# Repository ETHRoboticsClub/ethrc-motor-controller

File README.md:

<h1 align="center">ETHRC Motor Controller</h1>

<p align="center" width="100%">
  
</p>

***

<p align="center">
  
&nbsp; &nbsp; &nbsp; &nbsp;
  
</p>

***

## SPECIFICATIONS

| Parameter | ETHRC Motor Controller v1.0| 
| --- | --- |
| Voltage Input | 33 - 58.8V |
| Peak Electrical Power | TBD |
| Mass | TBD |
| Peak Phase Current | TBD |
| Communication | EtherCat, 5Mbps CAN-FD and SWD interface |
| Cooling | TBD|
| Positioning | 1x Onboard 14-bit Encoder and one external encoder |
| Control rate | TBD |
| PWM Switching Rate | TBD |
| MCU | STM32G474 |
| Dimensions | 88.0 × 88.0 mm |

***

## DIRECTORY STRUCTURE

    .
    ├─ Computations       # Misc calculations
    ├─ DXF_SVG            # Vector graphics
    ├─ HTML               # HTML files for generated webpage
    ├─ Images             # Pictures and renders
    │
    ├─ kibot_resources    # External resources for KiBot
    │  ├─ colors          # Color theme for KiCad
    │  ├─ fonts           # Fonts used in the project
    │  ├─ scripts         # External scripts used with KiBot
    │  └─ templates       # Templates for KiBot generated reports
    │
    ├─ kibot_yaml         # KiBot YAML config files
    ├─ KiRI               # KiRI (PCB diff viewer) files
    │
    ├─ lib                # KiCad footprint and symbol libraries
    │  ├─ 3d_models       # Component 3D models
    │  ├─ lib_fp          # Footprint libraries
    │  └─ lib_sym         # Symbol libraries
    │
    ├─ Logos              # Logos
    │
    ├─ Manufacturing      # Assembly and fabrication documents
    │  ├─ Assembly        # Assembly documents (BoM, pos, notes)
    │  │
    │  └─ Fabrication     # Fabrication documents (ZIP, notes)
    │     ├─ Drill Tables # CSV drill tables
    │     └─ Gerbers      # Gerbers
    │
    ├─ Report             # Reports for ERC/DRC
    ├─ Schematic          # PDF of schematic
    ├─ Templates          # Title block templates
    ├─ Testing
    │  └─ Testpoints      # Testpoints tables      
    │
    └─ Variants           # Outputs for assembly variants

***

## FIRMWARE

***

## CREDITS

Schematic is largely inspired by the moteus controllers designed by Josh Pieper and amulet motion controller designed by Vincent Nguyen. They were modified to meet our own specifications. The CI/CD workflow and the templates for this KiCad 9.0 project was forked from https://github.com/nguyen-v/KDT_Hierarchical_KiBot created by Vincent Nguyen.
***

## PHOTOS

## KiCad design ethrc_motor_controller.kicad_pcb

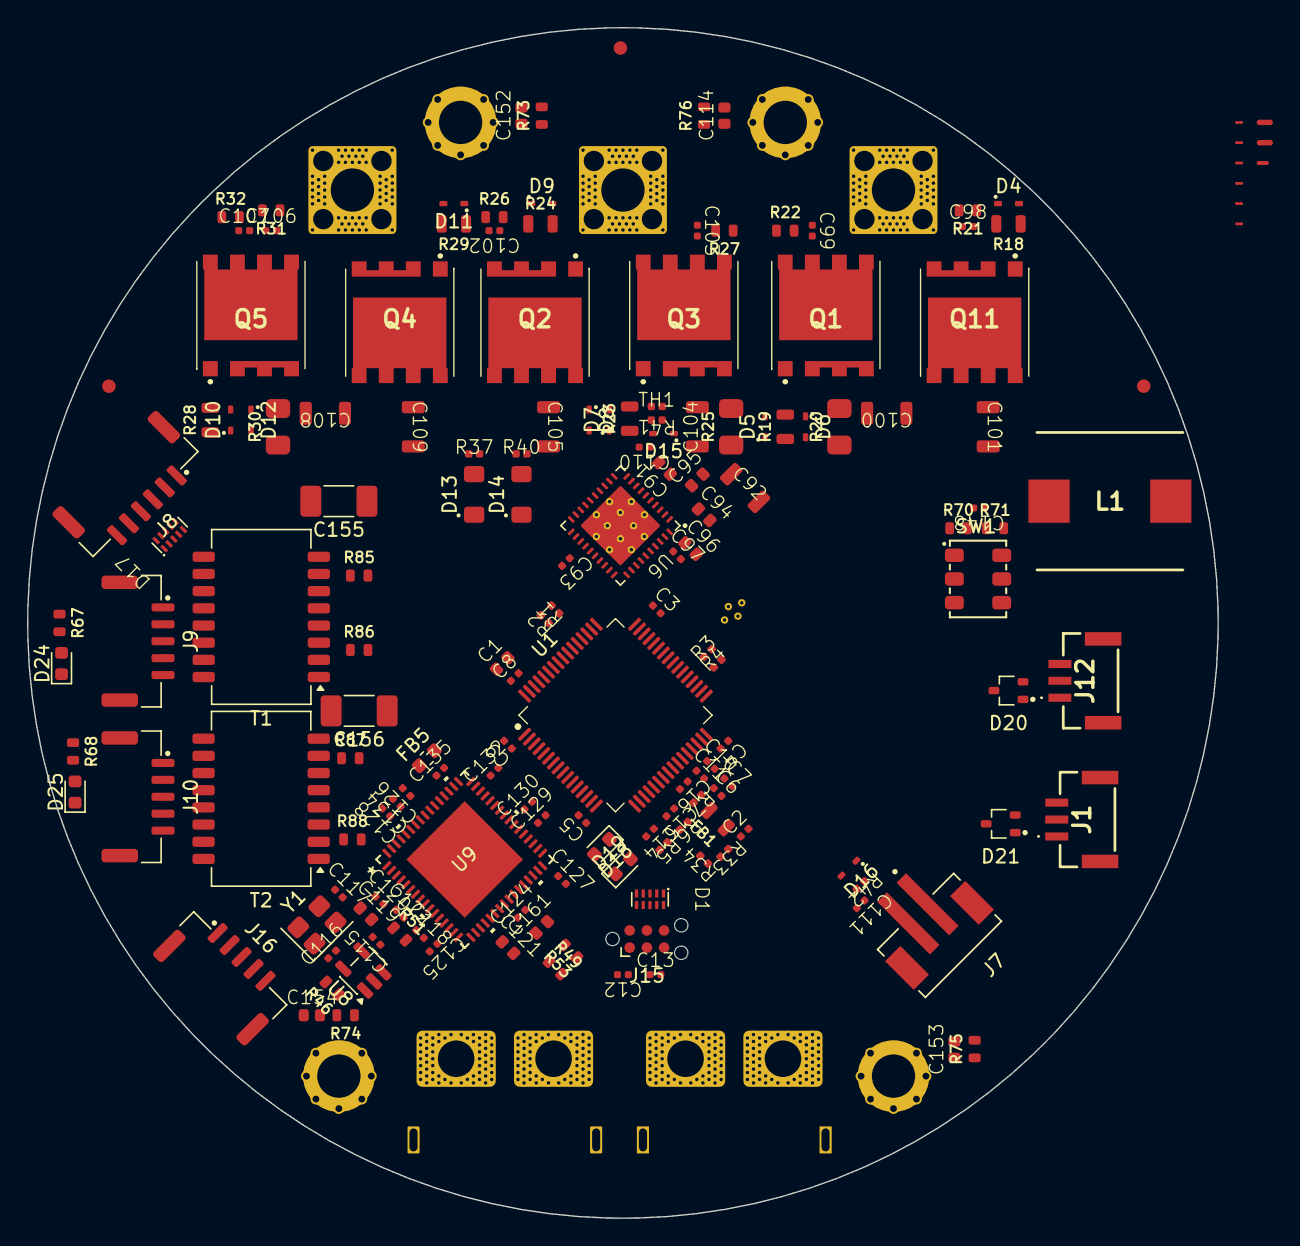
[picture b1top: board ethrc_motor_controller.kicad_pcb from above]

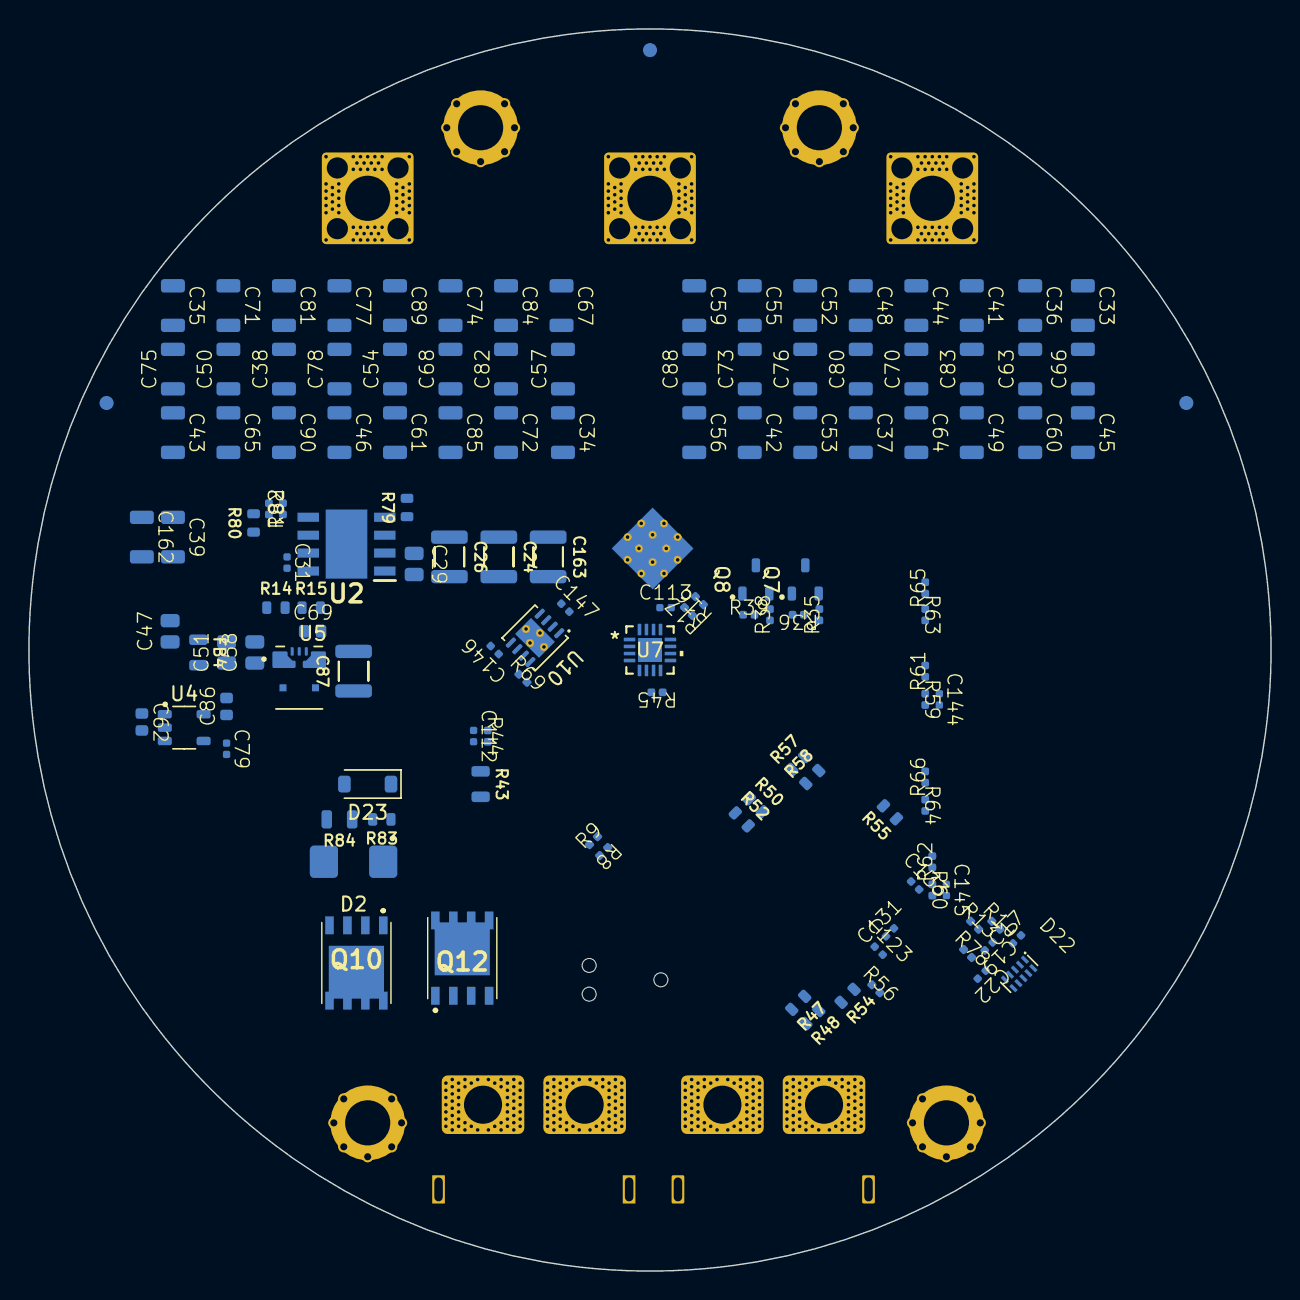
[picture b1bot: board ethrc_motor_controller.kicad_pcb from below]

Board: 6 copper layers, 88.0 x 88.0 mm, 306 parts (131 on the bottom side), 158 nets, no tracks yet.

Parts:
C1, C86: 4u7 X7R 16V; C_0603_1608_DensityHigh
C2, C6, C9: 1u X7R 10V; C_0402_1005_DensityHigh
C3, C4, C5, C8, C10, C11, C12, C13, C110, C111, C112, C146, C147: 100n X7R 50V; C_0402_1005_DensityHigh
C7: 4u7 X5R 25V; C_0402_1005_DensityHigh
C14, C15, C16: 1n X7R 25V; C_0402_1005_DensityHigh
C17, C19, C22: 1n; C_0402_1005_DensityHigh
C24, C26, C163: 1u; C_1210_3225_DensityHigh
C29, C58: 100n; C_0805_2012_DensityHigh
C31, C115, C118, C120, C122, C123, C124, C125, C126, C127, C128, C129, C130, C131, C132, C133, C134, C135: 100n; C_0402_1005_DensityHigh
C33, C34, C35, C36, C37, C38, C41, C42, C43, C44, C45, C46, C48, C49, C50, C52, C53, C54, C55, C56, C57, C59, C60, C61, C63, C64, C65, C66, C67, C68, C70, C71, C72, C73, C74, C75, C76, C77, C78, C80, C81, C82, C83, C84, C85, C88, C89, C90: 4u7 X7R 100V; C_1206_3216_DensityHigh
C39, C162: 47u; C_1206_3216_DensityHigh
C47: 2u2 X7R 100V; C_0805_2012_DensityHigh
C51: 10u; C_0805_2012_DensityHigh
C62, C91, C96: 1u X7R 25V; C_0603_1608_DensityHigh
C69: 10n; C_0603_1608_DensityHigh
C79: 10n X7R 100V; C_0402_1005_DensityHigh
C87: 22u; C_1210_3225_DensityHigh
C92, C101, C105, C109: 4u7 X7R 100V; C_1206_3216_DensityHighest
C93: 100n X7R 16V; C_0402_1005_DensityHigh
C94: 47n X7R 100V; C_0603_1608_DensityHigh
C95: 100n X7R 100V; C_0603_1608_DensityHigh
C97: 1u X7R 6.3V; C_0402_1005_DensityHigh
C98, C99, C102, C103, C106, C107: 3n3 X7R 100V; C_0402_1005_DensityHigh
C100, C104, C108: 100n X7R 100V; C_1206_3216_DensityHighest
C113: 1u; C_0402_1005_DensityHigh
C114, C152, C153, C154: 1n X7R 1kV; C_0603_1608_DensityHigh
C116, C117: 10p C0G; C_0402_1005_DensityHigh
C119, C121, C161: 1u; C_0603_1608_DensityHigh
C144, C145: 0.022u; C_0402_1005_DensityHigh
C148: 4n7 X7R 100V; C_0402_1005_DensityHigh
C155, C156: 1n X7R 2kV; C_1808_4520Metric
D1: PESD4USB3U-TBSX; SOT1176D
D2: SMBJ60A; D_SMB
D4, D5, D6, D7, D8, D9, D10, D11, D12, D15, D16: BAT41KFILM; D_SOD-523
D13: YELLOW; LED_SM1206
D14: GREEN; LED_SM1206
D17: PESD4USB5B-TBSX; SOT1176D
D18: Red; LED_0603_1608Metric
D19, D24, D25: Green; LED_0603_1608Metric
D20, D21: PESD2CANFD24V-UX; SOT95P230X117-3N
D22: PESD4USB5B; SOT1176D
D23: BZT52C15; D_SOD-123
FB1, FB4: 1k @ 100MHz; R_0805_2012_DensityHigh
FB5: 600R@100MHz; L_0603_1608Metric
FM1, FM2, FM3, FM4, FM5, FM6: Fiducial; Fiducial_1mm_Mask2mm
H1, H2, H3, H4: M3; MountingHole_3.2mm_M3_Pad_Via
J1, J12: Conn_01x03_Mounting; JST_GH_SM03B-GHS-TB_1x03-1MP_P1.25mm_Horizontal
J2: XT60PW-F; AMASS_XT60PW-F_1x02_P7.20mm_Horizontal
J3: XT60PW-M; AMASS_XT60PW-M_1x02_P7.20mm_Horizontal
J4: Phase A; Pad_Square_Vias_6.5x6.5mm
J5: Phase B; Pad_Square_Vias_6.5x6.5mm
J6: Phase C; Pad_Square_Vias_6.5x6.5mm
J7: S2B-PH-SM4-TB; JST_B2B-PH-SM4-TB
J8: Conn_01x06_Shield_Mounting; JST_GH_SM06B-GHS-TB_1x06-1MP_P1.25mm_Horizontal
J9, J10: SM05B-GHS-TB; JST_GH_SM05B-GHS-TB_1x05-1MP_P1.25mm_Horizontal
J15: Conn_ARM_SWD_TagConnect_TC2030-NL; Tag-Connect_TC2030-IDC-NL_2x03_P1.27mm_Vertical
J16: Conn_01x05_Mounting; JST_GH_SM05B-GHS-TB_1x05-1MP_P1.25mm_Horizontal
L1: 22u; INDPM108102X400N
NT3: SHNTA_P; NetTie-2_SMD_Pad0.2mm
NT4: SRC_HS_A; NetTie-2_SMD_Pad0.4mm
NT5: SHNTA_N; NetTie-2_SMD_Pad0.2mm
NT6: SHNTB_P; NetTie-2_SMD_Pad0.2mm
NT7: SHNTB_N; NetTie-2_SMD_Pad0.2mm
NT8: SRC_HS_B; NetTie-2_SMD_Pad0.3mm
NT9: SHNTC_P; NetTie-2_SMD_Pad0.2mm
NT10: SHNTC_N; NetTie-2_SMD_Pad0.2mm
NT11: SRC_HS_C; NetTie-2_SMD_Pad0.4mm
Q1, Q2, Q3, Q4, Q5, Q11: FDMT80080DC; FDMT80040DC
Q7, Q8: PMV90ENER; SOT-23-3
Q10, Q12: FDMS86163P; FDMS1D4N03S
R1, R2, R3, R4, R5, R6, R7, R45, R56: 22R 1%; R_0402_1005_DensityHigh
R8, R9: 22; R_0402_1005_DensityHigh
R10, R13, R78, R82: 10k; R_0402_1005_DensityHigh
R14: 15.8k; R_0603_1608_DensityHigh
R15, R46, R48, R49, R51, R57, R58: 10k; R_0603_1608_DensityHigh
R16, R17: 2k 1%; R_0402_1005_DensityHigh
R18, R19, R23, R24, R28, R29: 7R5 1% 1/2W; R_0805_2012_DensityHigh
R20, R25, R30: 0m5 1% 2W; HCS1206FTL500
R21, R22, R26, R27, R31, R32: 5R 1% 0.4W; R_0603_1608_DensityHigh
R33, R34, R35, R38: 100k 1%; R_0402_1005_DensityHigh
R36, R37, R39: 100R 1% 1/5W; R_0402_1005_DensityHigh
R40: 150R 1% 1/5W; R_0402_1005_DensityHigh
R41, R42, R69: 10k 1%; R_0402_1005_DensityHigh
R43: 100k 1%; R_0805_2012_DensityHigh
R44: 4k7 1%; R_0402_1005_DensityHigh
R47, R50, R52, R53: 2.2k; R_0603_1608_DensityHigh
R54: 1k; R_0603_1608_DensityHigh
R55: 12.1k 1%; R_0603_1608_DensityHigh
R59, R60, R61, R62, R63, R64, R65, R66: 49.9 1%; R_0402_1005_DensityHigh
R67, R68: 330; R_0603_1608_DensityHigh
R70, R71: 60R4 1% 1/4W; R_0603_1608_DensityHigh
R73, R74, R75, R76: 0R; R_0603_1608_DensityHigh
R79: 64.9k; R_0603_1608_DensityHigh
R80, R83: 100k; R_0603_1608_DensityHigh
R81: 40.2k; R_0402_1005_DensityHigh
R84: 220k; R_0805_2012_DensityHigh
R85, R86, R87, R88: 75 1%; R_0603_1608_DensityHigh
SW1: CAS-220TA; CAS-220A_NDC-L
T1, T2: H1102NL; Transformer_Pulse_H1100NL
TH1: 47k 1% NTC; R_0402_1005_DensityHigh
U1: STM32G474RET3; LQFP-64_10x10mm_P0.5mm
U2: LMR38020SDDAR; LMR38020
U4: LP2992IM5-3.3/NOPB; SOT95P280X145-5N
U5: TPSM861253RDXR; VREG_TPSM861253RDXR
U6: DRV8353FS; WQFN-40-1EP_6x6mm_P0.5mm_EP4.15x4.15mm_ThermalVias
U7: MA732GQ-Z; QFN-16_MA732
U8: 24LC32AT-I/OT; SOT-23-5
U9: LAN9253-V/R4X; QFN64_R4X_MCH
U10: TCAN1051HGVDRBRQ1; HVSON-8-1EP_3x3mm_P0.65mm_EP1.6x2.4mm_ThermalVias
Y1: 25MHz 8pF; Crystal_SMD_3225-4Pin_3.2x2.5mm

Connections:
+1V2_ESC: C122.1, C124.1, C126.1, C128.1, C130.1, C161.1, U9.6 (VDDCR), U9.24 (VDDCR), U9.38 (VDDCR), U9.56 (VDD12TX1), U9.59 (VDD12TX2)
+3V3: C1.1, C3.1, C4.1, C5.1, C8.1, C9.1, C12.1, C87.1, C113.1, C115.2, C121.1, C123.1, C125.1, C127.1, C129.1, C131.1, C132.1, C146.1, D19.2 (A), FB5.2, J8.1, J15.1 (VCC), R10.1, R13.1, R16.1, R17.1, R49.2, R50.1, R51.1, R52.1, R78.1, U1.1 (VBAT), U1.16 (VDD), U1.32 (VDD), U1.48 (VDD), U1.64 (VDD), U5.3 (VOUT), U5.7 (VOS), U7.13 (VDD), U8.4 (VCC), U9.5 (VDD33), U9.7 (REG_EN), U9.14 (VDDIO), U9.20 (VDDIO), U9.32 (VDDIO), U9.37 (VDDIO), U9.47 (VDDIO), U10.5 (VIO)
+3V3_PHY: C133.1, C134.1, C135.1, C144.1, C145.1, FB5.1, R59.1, R60.1, R61.1, R62.1, R63.1, R64.1, R65.1, R66.1, T1.2 (TCT), T1.7 (RCT), T2.2 (TCT), T2.7 (RCT), U9.51 (VDD33TXRX1), U9.58 (VDD33BIAS), U9.64 (VDD33TXRX2)
+5V: C39.1, C47.1, C62.1, C147.1, C162.1, FB4.1, J16.1, L1.2, R37.2, R40.1, R80.2, R81.1, U4.1 (VIN), U4.3 (ON/~OFF), U10.3 (VCC)
+A3V3: C2.1, C86.1, C93.1, D15.1 (K), D16.1 (K), FB1.1, R33.1, R41.1, R42.1, U4.5 (VOUT), U6.24 (VREF)
+VBAT: C24.1, C26.1, C29.1, C33.1, C34.1, C35.1, C36.1, C37.1, C38.1, C41.1, C42.1, C43.1, C44.1, C45.1, C46.1, C48.1, C49.1, C50.1, C52.1, C53.1, C54.1, C55.1, C56.1, C57.1, C59.1, C60.1, C61.1, C63.1, C64.1, C65.1, C66.1, C67.1, C68.1, C70.1, C71.1, C72.1, C73.1, C74.1, C75.1, C76.1, C77.1, C78.1, C80.1, C81.1, C82.1, C83.1, C84.1, C85.1, C88.1, C89.1, C90.1, C91.1, C92.1, C95.1, C100.1, C101.1, C104.1, C105.1, C108.1, C109.1, C163.1, D2.1 (K), D23.1 (K), Q2.5, Q2.6, Q2.7, Q2.8, Q4.5, Q4.6, Q4.7, Q4.8, Q10.1 (S), Q10.2 (S), Q10.3 (S), Q11.5, Q11.6, Q11.7, Q11.8, Q12.1 (S), Q12.2 (S), Q12.3 (S), R21.2, R26.2, R31.2, R43.1, R83.1, U2.2 (EN), U2.3 (VIN), U6.3 (VM), U6.4 (VDRAIN)
/Project Architecture/Comms - EtherCat/ECAT_P0_CBL_RX+: J9.3, T1.11 (RX+)
/Project Architecture/Comms - EtherCat/ECAT_P0_CBL_RX-: J9.2, T1.9 (RX-)
/Project Architecture/Comms - EtherCat/ECAT_P0_CBL_TX+: J9.5, T1.16 (TX+)
/Project Architecture/Comms - EtherCat/ECAT_P0_CBL_TX-: J9.4, T1.14 (TX-)
/Project Architecture/Comms - EtherCat/ECAT_P0_RX+: R63.2, T1.6 (RD+), U9.55 (RXPA)
/Project Architecture/Comms - EtherCat/ECAT_P0_RX-: R65.2, T1.8 (RD-), U9.54 (RXNA)
/Project Architecture/Comms - EtherCat/ECAT_P0_TX+: R59.2, T1.1 (TD+), U9.53 (TXPA)
/Project Architecture/Comms - EtherCat/ECAT_P0_TX-: R61.2, T1.3 (TD-), U9.52 (TXNA)
/Project Architecture/Comms - EtherCat/ECAT_P1_CBL_RX+: J10.3, T2.11 (RX+)
/Project Architecture/Comms - EtherCat/ECAT_P1_CBL_RX-: J10.2, T2.9 (RX-)
/Project Architecture/Comms - EtherCat/ECAT_P1_CBL_TX+: J10.5, T2.16 (TX+)
/Project Architecture/Comms - EtherCat/ECAT_P1_CBL_TX-: J10.4, T2.14 (TX-)
/Project Architecture/Comms - EtherCat/ECAT_P1_RX+: R64.2, T2.6 (RD+), U9.60 (RXPB)
/Project Architecture/Comms - EtherCat/ECAT_P1_RX-: R66.2, T2.8 (RD-), U9.61 (RXNB)
/Project Architecture/Comms - EtherCat/ECAT_P1_TX+: R60.2, T2.1 (TD+), U9.62 (TXPB)
/Project Architecture/Comms - EtherCat/ECAT_P1_TX-: R62.2, T2.3 (TD-), U9.63 (TXNB)
/Project Architecture/Comms - EtherCat/EE_SCL: R50.2, U8.1 (SCL), U9.43 (EESCL/EE_EMUL2)
/Project Architecture/Comms - EtherCat/EE_SDA: R52.2, U8.3 (SDA), U9.42 (EESDA/EE_EMUL1)
/Project Architecture/Comms - EtherCat/ESC_CLK25: R54.1, U9.8 (CLK_25/XTAL_MODE)
/Project Architecture/Comms - EtherCat/ESC_CS: U1.34 (PB12), U9.50 (SCS#)
/Project Architecture/Comms - EtherCat/ESC_ERR: R47.1, R48.1, U9.9 (ERRLED/100FD_B)
/Project Architecture/Comms - EtherCat/ESC_IRQ: U1.41 (PC9), U9.44 (IRQ)
/Project Architecture/Comms - EtherCat/ESC_LINK0: R58.1, R67.1, U9.48 (LINKACTLED0/CHIP_MODE0)
/Project Architecture/Comms - EtherCat/ESC_LINK1: R57.1, R68.1, U9.46 (LINKACTLED1/CHIP_MODE1)
/Project Architecture/Comms - EtherCat/ESC_MISO: R56.2, U1.36 (PB14)
/Project Architecture/Comms - EtherCat/ESC_MISO_ESC: R56.1, U9.13 (SO/SIO1)
/Project Architecture/Comms - EtherCat/ESC_MOSI: R3.2, U9.17 (SI/SIO0)
/Project Architecture/Comms - EtherCat/ESC_OSCVDD12: C119.1, C120.1, U9.3 (OSCVDD12)
/Project Architecture/Comms - EtherCat/ESC_RBIAS: R55.1, U9.57 (RBIAS)
/Project Architecture/Comms - EtherCat/ESC_RST: C118.1, R51.2, U1.44 (PA10), U9.11 (RST#)
/Project Architecture/Comms - EtherCat/ESC_RUN: R49.1, R53.2, U9.45 (RUNLED/E2PSIZE)
/Project Architecture/Comms - EtherCat/ESC_SCLK: R4.2, U9.19 (SCK)
/Project Architecture/Comms - EtherCat/ESC_SYNC0: U1.39 (PC7), U9.34 (SYNC0/LATCH0)
/Project Architecture/Comms - EtherCat/ESC_SYNC1: U1.40 (PC8), U9.18 (SYNC1/LATCH1)
/Project Architecture/Comms - EtherCat/ESC_XI: C117.1, U9.1 (OSCI), Y1.3
/Project Architecture/Comms - EtherCat/ESC_XO: C116.1, U9.2 (OSCO), Y1.1
/Project Architecture/Comms - FD-CAN/CAN_TERM_B: R71.2, SW1.4 (A)
/Project Architecture/Comms - FD-CAN/CAN_TERM_MID: C148.1, R70.2, R71.1
/Project Architecture/Comms - FD-CAN/CAN_TERM_T: R70.1, SW1.1 (A)
/Project Architecture/Comms - FD-CAN/FDCAN+: D20.1 (K1), D21.1 (K1), J1.1, J12.1, SW1.2 (B), U10.7 (CANH)
/Project Architecture/Comms - FD-CAN/FDCAN-: D20.2 (K2), D21.2 (K2), J1.2, J12.2, SW1.5 (B), U10.6 (CANL)
/Project Architecture/Comms - FD-CAN/FDCAN_RX: U1.58 (PB5), U10.4 (RXD)
/Project Architecture/Comms - FD-CAN/FDCAN_S: R69.1, U10.8 (S)
/Project Architecture/Comms - FD-CAN/FDCAN_TX: U1.59 (PB6), U10.1 (TXD)
/Project Architecture/MCU - IOs/BOARD_VERSION: R33.2, R34.1, U1.18 (PA4)
/Project Architecture/MCU - IOs/DRV_CS: U1.24 (PB0), U6.30 (nSCS)
/Project Architecture/MCU - IOs/DRV_MISO: R17.2, U1.53 (PC11), U6.27 (SDO)
/Project Architecture/MCU - IOs/DRV_MOSI: R2.1, U6.28 (SDI)
/Project Architecture/MCU - IOs/DRV_MOSI_MCU: R2.2, U1.54 (PC12)
/Project Architecture/MCU - IOs/DRV_SCLK: R1.1, U6.29 (SCLK)
/Project Architecture/MCU - IOs/DRV_SCLK_MCU: R1.2, U1.52 (PC10)
/Project Architecture/MCU - IOs/ENC_BRD_CS: U1.26 (PB2), U7.5 (CS)
/Project Architecture/MCU - IOs/ENC_EXT_CS: D17.1 (K), D17.10 (K), J8.6, U1.51 (PA15)
/Project Architecture/MCU - IOs/ENC_MISO: D17.4 (K), D17.7 (K), J8.4, R45.1, U1.57 (PB4)
/Project Architecture/MCU - IOs/ENC_MOSI: D17.2 (K), D17.9 (K), J8.5, R9.2, U7.4 (MOSI)
/Project Architecture/MCU - IOs/ENC_MOSI_MCU: R9.1, U1.21 (PA7)
/Project Architecture/MCU - IOs/ENC_SCLK: D17.5 (K), D17.6 (K), J8.3, R8.2, U7.12 (SCLK)
/Project Architecture/MCU - IOs/ENC_SCLK_MCU: R8.1, U1.19 (PA5)
/Project Architecture/MCU - IOs/ESC_MOSI_MCU: R3.1, U1.37 (PB15)
/Project Architecture/MCU - IOs/ESC_SCLK_MCU: R4.1, U1.35 (PB13)
/Project Architecture/MCU - IOs/FILTER_SOA: C14.1, R5.1, U1.17 (PA3)
/Project Architecture/MCU - IOs/FILTER_SOB: C15.1, R6.1, U1.20 (PA6)
/Project Architecture/MCU - IOs/FILTER_SOC: C16.1, R7.1, U1.25 (PB1)
/Project Architecture/MCU - IOs/HALL_A: C17.1, D22.1 (K), D22.10 (K), J16.3, R10.2, U1.60 (PB7)
/Project Architecture/MCU - IOs/HALL_B: C19.1, D22.2 (K), D22.9 (K), J16.4, R13.2, U1.45 (PA11)
/Project Architecture/MCU - IOs/HALL_C: C22.1, D22.4 (K), D22.7 (K), J16.5, R78.2, U1.46 (PA12)
/Project Architecture/MCU - IOs/LED_DBG: R35.1, R36.1, U1.30 (PB10)
/Project Architecture/MCU - IOs/LED_PWR: R38.1, R39.1, U1.38 (PC6)
/Project Architecture/MCU - IOs/MOTOR_ENABLE: U1.3 (PC14), U6.31 (ENABLE)
/Project Architecture/MCU - IOs/MOTOR_FAULT: R16.2, U1.8 (PC0), U6.26 (nFAULT)
/Project Architecture/MCU - IOs/MOTOR_HIZ: U1.4 (PC15), U6.33 (INLA), U6.35 (INLB), U6.37 (INLC)
/Project Architecture/MCU - IOs/NRST: C13.1, D1.1 (K), D1.10 (K), J15.3 (~RESET), U1.7 (PG10)
/Project Architecture/MCU - IOs/PWM_PHASEA: U1.14 (PA2), U6.32 (INHA)
/Project Architecture/MCU - IOs/PWM_PHASEB: U1.13 (PA1), U6.34 (INHB)
/Project Architecture/MCU - IOs/PWM_PHASEC: U1.12 (PA0), U6.36 (INHC)
/Project Architecture/MCU - IOs/SENSE_TEMP_FET: C110.1, D15.2 (A), R41.2, TH1.1, U1.33 (PB11)
/Project Architecture/MCU - IOs/SENSE_TEMP_MOT: C111.1, D16.2 (A), J7.1, R42.2, U1.42 (PA8)
/Project Architecture/MCU - IOs/SENSE_VBAT: C112.1, R43.2, R44.1, U1.43 (PA9)
/Project Architecture/MCU - IOs/SOA: R5.2, U6.23 (SOA)
/Project Architecture/MCU - IOs/SOB: R6.2, U6.22 (SOB)
/Project Architecture/MCU - IOs/SOC: R7.2, U6.21 (SOC)
/Project Architecture/MCU - IOs/SWCLK: D1.4 (K), D1.7 (K), J15.4 (SWCLK), U1.50 (PA14)
/Project Architecture/MCU - IOs/SWDIO: D1.5 (K), D1.6 (K), J15.2 (SWDIO), U1.49 (PA13)
/Project Architecture/MCU - Power/F_A3V3: C6.1, C7.1, C10.1, C11.1, FB1.2, U1.28 (VREF+), U1.29 (VDDA)
/Project Architecture/Motor Control - Top Level/CPH: C94.1, U6.2 (CPH)
/Project Architecture/Motor Control - Top Level/CPL: C94.2, U6.1 (CPL)
/Project Architecture/Motor Control - Top Level/DVDD: C97.1, U6.38 (DVDD)
/Project Architecture/Motor Control - Top Level/GHA: D4.1 (K), R18.2, U6.6 (GHA)
/Project Architecture/Motor Control - Top Level/GHB: D9.1 (K), R24.1, U6.15 (GHB)
/Project Architecture/Motor Control - Top Level/GHC: D11.1 (K), R29.1, U6.16 (GHC)
/Project Architecture/Motor Control - Top Level/GLA: D5.1 (K), R19.1, U6.8 (GLA)
/Project Architecture/Motor Control - Top Level/GLB: D7.1 (K), R23.1, U6.13 (GLB)
/Project Architecture/Motor Control - Top Level/GLC: D10.1 (K), R28.1, U6.18 (GLC)
/Project Architecture/Motor Control - Top Level/Motor Control - Inverter/FET_GHA: D4.2 (A), Q11.1, R18.1
/Project Architecture/Motor Control - Top Level/Motor Control - Inverter/FET_GHB: D9.2 (A), Q2.1, R24.2
/Project Architecture/Motor Control - Top Level/Motor Control - Inverter/FET_GHC: D11.2 (A), Q4.1, R29.2
/Project Architecture/Motor Control - Top Level/Motor Control - Inverter/FET_GLA: D5.2 (A), D6.1 (K), Q1.1, R19.2
/Project Architecture/Motor Control - Top Level/Motor Control - Inverter/FET_GLB: D7.2 (A), D8.1 (K), Q3.1, R23.2
/Project Architecture/Motor Control - Top Level/Motor Control - Inverter/FET_GLC: D10.2 (A), D12.1 (K), Q5.1, R28.2
/Project Architecture/Motor Control - Top Level/Motor Control - Inverter/PHA: C98.1, C99.2, J4.1, NT4.2, Q1.5, Q1.6, Q1.7, Q1.8, Q11.2, Q11.3, Q11.4
/Project Architecture/Motor Control - Top Level/Motor Control - Inverter/PHB: C102.1, C103.2, J5.1, NT8.2, Q2.2, Q2.3, Q2.4, Q3.5, Q3.6, Q3.7, Q3.8
/Project Architecture/Motor Control - Top Level/Motor Control - Inverter/PHC: C106.1, C107.2, J6.1, NT11.2, Q4.2, Q4.3, Q4.4, Q5.5, Q5.6, Q5.7, Q5.8
/Project Architecture/Motor Control - Top Level/Motor Control - Inverter/SNUBH_A: C98.2, R21.1
/Project Architecture/Motor Control - Top Level/Motor Control - Inverter/SNUBH_B: C102.2, R26.1
/Project Architecture/Motor Control - Top Level/Motor Control - Inverter/SNUBH_C: C106.2, R31.1
/Project Architecture/Motor Control - Top Level/Motor Control - Inverter/SNUBL_A: C99.1, R22.2
/Project Architecture/Motor Control - Top Level/Motor Control - Inverter/SNUBL_B: C103.1, R27.2
/Project Architecture/Motor Control - Top Level/Motor Control - Inverter/SNUBL_C: C107.1, R32.2
/Project Architecture/Motor Control - Top Level/Motor Control - Inverter/SRC_LS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: C100.2, NT3.1, Q1.2, Q1.3, Q1.4, R20.2, R22.1
/Project Architecture/Motor Control - Top Level/Motor Control - Inverter/SRC_LS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: C104.2, NT6.2, Q3.2, Q3.3, Q3.4, R25.2, R27.1
/Project Architecture/Motor Control - Top Level/Motor Control - Inverter/SRC_LS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: C108.2, NT9.2, Q5.2, Q5.3, Q5.4, R30.2, R32.1
/Project Architecture/Motor Control - Top Level/SA+: NT3.2, U6.9 (SPA)
/Project Architecture/Motor Control - Top Level/SA-: NT5.1, U6.10 (SNA)
/Project Architecture/Motor Control - Top Level/SB+: NT6.1, U6.12 (SPB)
/Project Architecture/Motor Control - Top Level/SB-: NT7.1, U6.11 (SNB)
/Project Architecture/Motor Control - Top Level/SC+: NT9.1, U6.19 (SPC)
/Project Architecture/Motor Control - Top Level/SC-: NT10.1, U6.20 (SNC)
/Project Architecture/Motor Control - Top Level/SHA: NT4.1, U6.7 (SHA)
/Project Architecture/Motor Control - Top Level/SHB: NT8.1, U6.14 (SHB)
/Project Architecture/Motor Control - Top Level/SHC: NT11.1, U6.17 (SHC)
/Project Architecture/Motor Control - Top Level/VCP: C91.2, U6.5 (VCP)
/Project Architecture/Motor Control - Top Level/VGLS: C96.1, U6.40 (VGLS)
/Project Architecture/Power - Connectors/VBAT_IN: J2.2, J3.2, Q10.5 (D), Q10.6 (D), Q10.7 (D), Q10.8 (D), Q10.9 (D), Q12.5 (D), Q12.6 (D), Q12.7 (D), Q12.8 (D), Q12.9 (D)
/Project Architecture/Power - Generation/ADJ_A3V3: C79.1, U4.4 (ADJ)
/Project Architecture/Power - Generation/F_VIN_3V3: C51.1, C58.1, FB4.2, R14.1, U5.1 (VIN)
/Project Architecture/Power - Generation/SW_5V: C31.2, L1.1, U2.8 (SW)
/Project Architecture/Sensing - Position/ENC_MISO_IC: R45.2, U7.7 (MISO)
/Project Architecture/User - LED Indicators/DBG_G: Q7.1 (G), R36.2
/Project Architecture/User - LED Indicators/LED_DBG_A: D13.2 (A), R37.1
/Project Architecture/User - LED Indicators/LED_DBG_K: D13.1 (K), Q7.3 (D)
/Project Architecture/User - LED Indicators/LED_PWR_A: D14.2 (A), R40.2
/Project Architecture/User - LED Indicators/LED_PWR_K: D14.1 (K), Q8.3 (D)
/Project Architecture/User - LED Indicators/PWR_G: Q8.1 (G), R39.2
CHASSIS: C114.1, C152.1, C153.1, C154.1, C155.2, C156.2, D17.3 (A), D17.8 (A), D20.3 (CC), D21.3 (CC), D22.3 (A), D22.8 (A), H1.1, H2.1, H3.1, H4.1, J2.MP2, J3.MP2, J7.S1, J7.S2, J8.MP1, J8.MP2, J9.1, J9.MP1, J9.MP2, J10.1, J10.MP1, J10.MP2, J16.MP1, J16.MP2, R73.1, R74.1, R75.1, R76.1
GND: C1.2, C2.2, C3.2, C4.2, C5.2, C6.2, C7.2, C8.2, C9.2, C10.2, C11.2, C12.2, C13.2, C14.2, C15.2, C16.2, C17.2, C19.2, C22.2, C24.2, C26.2, C29.2, C33.2, C34.2, C35.2, C36.2, C37.2, C38.2, C39.2, C41.2, C42.2, C43.2, C44.2, C45.2, C46.2, C47.2, C48.2, C49.2, C50.2, C51.2, C52.2, C53.2, C54.2, C55.2, C56.2, C57.2, C58.2, C59.2, C60.2, C61.2, C62.2, C63.2, C64.2, C65.2, C66.2, C67.2, C68.2, C69.2, C70.2, C71.2, C72.2, C73.2, C74.2, C75.2, C76.2, C77.2, C78.2, C79.2, C80.2, C81.2, C82.2, C83.2, C84.2, C85.2, C86.2, C87.2, C88.2, C89.2, C90.2, C92.2, C93.2, C95.2, C96.2, C97.2, C101.2, C105.2, C109.2, C110.2, C111.2, C112.2, C113.2, C114.2, C115.1, C116.2, C117.2, C118.2, C119.2, C120.2, C121.2, C122.2, C123.2, C124.2, C125.2, C126.2, C127.2, C128.2, C129.2, C130.2, C131.2, C132.2, C133.2, C134.2, C135.2, C144.2, C145.2, C146.2, C147.2, C148.2, C152.2, C153.2, C154.2, C161.2, C162.2, C163.2, D1.3 (A), D1.8 (A), D2.2 (A), D6.2 (A), D8.2 (A), D12.2 (A), D18.1 (K), D24.1 (K), D25.1 (K), J1.3, J2.1, J3.1, J7.2, J8.2, J12.3, J15.5 (GND), J16.2, NT5.2, NT7.2, NT10.2, Q7.2 (S), Q8.2 (S), R15.2, R20.1, R25.1, R30.1, R34.2, R35.2, R38.2, R44.2, R46.1, R48.2, R54.2, R55.2, R57.2, R58.2, R69.2, R73.2, R74.2, R75.2, R76.2, R79.2, R82.2, R84.2, TH1.2, U1.15 (VSS), U1.27 (VSSA), U1.31 (VSS), U1.47 (VSS), U1.63 (VSS), U2.1 (GND), U2.9 (EP), U4.2 (GND), U5.4 (PGND), U6.25 (AGND), U6.39 (GND), U6.41 (EP), U7.8 (GND), U7.17 (PAD), U8.2 (VSS), U9.4 (OSCVSS), U9.41 (TESTMODE), U9.65 (VSS(EP)), U10.2 (GND), U10.9 (PAD), Y1.2, Y1.4
unnamed: C155.1, R85.2, R86.2
unnamed: C156.1, R87.2, R88.2
unnamed: D18.2 (A), R47.2
unnamed: D19.1 (K), R53.1
unnamed: D23.2 (A), Q10.4 (G), Q12.4 (G), R83.2, R84.1
unnamed: D24.2 (A), R67.2
unnamed: D25.2 (A), R68.2
unnamed: R86.1, T1.10 (RXCT)
unnamed: R85.1, T1.15 (TXCT)
unnamed: R88.1, T2.10 (RXCT)
unnamed: R87.1, T2.15 (TXCT)
unnamed: C31.1, U2.7 (BOOT)
unnamed: R81.2, R82.1, U2.5 (FB)
unnamed: R80.1, U2.6 (PG)
unnamed: R79.1, U2.4 (RT/SYNC)
unnamed: C69.1, R14.2, R15.1, U5.6 (EN)
unnamed: R46.2, U8.5 (WP)

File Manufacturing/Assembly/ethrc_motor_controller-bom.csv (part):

Row,Quantity Per PCB,References,Value,Datasheet,Footprint,Description,Manufacturer,Manufacturer Part Number,Supplier 1,Supplier Part Number 1
1,2,C116 C117,10p C0G,,C_0402_1005_DensityHigh,"10 pF ±5% 50V Ceramic Capacitor C0G, NP0 0402 (1005 Metric)",Samsung Electro-Mechanics,CL05C100JB5NNNC,Mouser,187-CL05C100JB5NNNC
2,6,C14 C15 C16 C17 C19 C22,1n X7R 25V,https://www.yageo.com/upload/media/product/app/datasheet/mlc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,C_0402_1005_DensityHigh,1000 pF ±10% 25V Ceramic Capacitor X7R 0402 (1005 Metric) Unpolarized capacitor,YAGEO,AC0402KRX7R8BB102,Digikey,311-3065-1-ND
3,6,C98 C99 C102 C103 C106 C107,3n3 X7R 100V,https://search.murata.co.jp/Ceramy/image/img/A01X/G101/ENG/G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,C_0402_1005_DensityHigh,3300 pF ±10% 100V Ceramic Capacitor X7R 0402 (1005 Metric),Murata Electronics,GRM155R72A332KA01D,Digikey,490-8261-1-ND
4,1,C148,4n7 X7R 100V,https://www.murata.com/-/media/webrenewal/support/library/ca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,C_0402_1005_DensityHigh,4700 pF ±10% 100V Ceramic Capacitor X7R 0402 (1005 Metric),Murata Electronics,GCM155R72A472KA37D,Digikey,490-4765-1-ND
5,2,C69 C79,10n,~,C_0603_1608_DensityHigh,Unpolarized capacitor 10000 pF ±10% 100V Ceramic Capacitor X7R 0402 (1005 Metric),Taiyo Yuden,HMR105B7103KV-F,Digikey,587-HMR105B7103KV-FCT-ND
6,2,C144 C145,0.022u,~,C_0402_1005_DensityHigh,0.022 µF ±10% 50V Ceramic Capacitor X7R 0402 (1005 Metric) Automotive AEC-Q200,Murata Electronics,GCM155R71H223KA55D,Mouser,81-GCM155R71H223KA5D
7,1,C94,47n X7R 100V,https://connect.kemet.com:7667/gateway/IntelliData-Component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,C_0603_1608_DensityHigh,0.047 µF ±10% 100V Ceramic Capacitor X7R 0603 (1608 Metric),KEMET,C0603C473K1RECAUTO,Digikey,399-14764-1-ND
8,16,C3 C4 C5 C8 C10 C11 C12 C13 C29 C31 C58 C110 C111 C112 C146 C147,100n X7R 50V,https://search.murata.co.jp/Ceramy/image/img/A01X/G101/ENG/G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,C_0402_1005_DensityHigh,0.1 µF ±10% 50V Ceramic Capacitor X7R 0402 (1005 Metric) 0.1 µF ±10% 100V Ceramic Capacitor X7R 0805 (2012 Metric) 0.1 µF ±10% 16V Ceramic Capacitor X7R 0402 (1005 Metric) Unpolarized capacitor,Murata Electronics,GCM155R71H104KE02J,Digikey,490-14514-1-ND
9,3,C100 C104 C108,100n X7R 100V,https://connect.kemet.com:7667/gateway/IntelliData-Component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,C_1206_3216_DensityHighest,0.1 µF ±10% 100V Ceramic Capacitor X7R 1206 (3216 Metric),KEMET,C1206C104K1RACAUTO,Digikey,399-7008-1-ND
10,17,C115 C118 C120 C122 C123 C124 C125 C126 C127 C128 C129 C130 C131 C132 C133 C134 C135,100n,,C_0402_1005_DensityHigh,0.1 µF ±10% 16V Ceramic Capacitor X7R 0402 (1005 Metric),Samsung Electro-Mechanics,CL05B104KO5NNNC,Mouser,187-CL05B104KO5NNNC
11,1,C93,100n X7R 16V,https://search.murata.co.jp/Ceramy/image/img/A01X/G101/ENG/G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,C_0402_1005_DensityHigh,0.1 µF ±10% 16V Ceramic Capacitor X7R 0402 (1005 Metric),Murata Electronics,GCM155R71C104KA55D,Digikey,490-4759-1-ND
12,1,C95,100n X7R 100V,https://mm.digikey.com/Volume0/opasdata/d220001/medias/docus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,C_0603_1608_DensityHigh,0.1 µF ±10% 100V Ceramic Capacitor X7R 0603 (1608 Metric),Taiyo Yuden,HMK107B7104KAHT,Digikey,587-6009-1-ND
13,14,C2 C6 C9 C24 C26 C62 C91 C96 C97 C113 C119 C121 C161 C163,1u X7R 10V,https://search.murata.co.jp/Ceramy/image/img/A01X/G101/ENG/G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,C_0402_1005_DensityHigh,1 µF ±10% 10V Ceramic Capacitor X7R 0402 (1005 Metric) 1 µF ±10% 100V Ceramic Capacitor X7R 1210 (3225 Metric) 1 µF ±10% 25V Ceramic Capacitor X7R 0603 (1608 Metric) 1 µF ±10% 6.3V Ceramic Capacitor X7R 0402 (1005 Metric) Unpolarized capacitor,Murata Electronics Taiyo Yuden Samsung Electro-Mechanics,GRM155Z71A105KE01J TMK107AB7105KAHT GRT155R70J105KE01D CL10B105KA8NNNC,Digikey Mouser,490-GRM155Z71A105KE01JCT-ND 587-3467-1-ND 490-18216-1-ND 187-CL10B105KA8NNNC
14,1,C47,2u2 X7R 100V,https://product.tdk.com/system/files/dam/doc/product/capacit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,C_0805_2012_DensityHigh,Multilayer Ceramic Capacitors MLCC - SMD/SMT 0805 100VDC 2.2uF 10% 1.25mm AEC-Q200,TDK Corporation,CGA4J1X7R2A225K125AC,Mouser,810-CGA4J7R2A225K125
15,2,C1 C86,4u7 X7R 16V,https://search.murata.co.jp/Ceramy/image/img/A01X/G101/ENG/G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,C_0603_1608_DensityHigh,4.7 µF ±10% 16V Ceramic Capacitor X7R 0603 (1608 Metric),Murata Electronics,GRM188Z71C475KE21J,Digikey,490-GRM188Z71C475KE21JCT-ND
16,52,C33 C34 C35 C36 C37 C38 C41 C42 C43 C44 C45 C46 C48 C49 C50 C52 C53 C54 C55 C56 C57 C59 C60 C61 C63 C64 C65 C66 C67 C68 C70 C71 C72 C73 C74 C75 C76 C77 C78 C80 C81 C82 C83 C84 C85 C88 C89 C90 C92 C101 C105 C109,4u7 X7R 100V,https://search.murata.co.jp/Ceramy/image/img/A01X/G101/ENG/G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,C_1206_3216_DensityHigh,4.7 µF ±10% 100V Ceramic Capacitor X7R 1206 (3216 Metric),Murata Electronics,GRJ31CZ72A475KE01L,Digikey,490-GRJ31CZ72A475KE01LCT-ND
17,1,C7,4u7 X5R 25V,https://www.mouser.ch/datasheet/2/40/CM_Series_e-2835982.pdf,C_0402_1005_DensityHigh,4.7 µF ±20% 25V Ceramic Capacitor X5R 0402 (1005 Metric),KYOCERA AVX,CM05X5R475M25AH,Mouser,581-CM05X5R475M25AH
18,1,C51,10u,~,C_0805_2012_DensityHigh,Unpolarized capacitor,,,,
19,2,C87 L1,22u,~,C_1210_3225_DensityHigh,Unpolarized capacitor 22 µH ±20% Shielded Molded Power Inductor 4.5 A 66 mOhm Max Nonstandard,,,,
20,2,C39 C162,47u,~,C_1206_3216_DensityHigh,47 µF ±10% 10V Ceramic Capacitor X5R 1206 (3216 Metric),,,,
21,4,C114 C152 C153 C154,1n X7R 1kV,https://connect.kemet.com:7667/gateway/IntelliData-Component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,C_0603_1608_DensityHigh,1000 pF ±10% 1000V (1kV) Ceramic Capacitor X7R 0603 (1608 Metric),KEMET,C0603V102KDRAC7867,Digikey,399-12306-1-ND
22,2,C155 C156,1n X7R 2kV,https://yageogroup.com/content/datasheet/asset/file/KEM_C101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,C_1808_4520Metric,1000 pF ±10% 2000V (2kV) Ceramic Capacitor X7R 1808 (4520 Metric),KEMET,C1808C102KGRACTU,Digikey,399-C1808C102KGRACTUCT-ND
23,11,D4 D5 D6 D7 D8 D9 D10 D11 D12 D15 D16,BAT41KFILM,https://www.st.com/content/ccc/resource/technical/document/d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,D_SOD-523,Diode 100 V 200mA Surface Mount SOD-523,STMicroelectronics,BAT41KFILM,Digikey,497-5556-1-ND
24,1,D23,BZT52C15,https://www.diodes.com/assets/Datasheets/ds18004.pdf,D_SOD-123,Zener Diode 15 V 500 mW ±5% Surface Mount SOD-123,Diodes Incorporated,BZT52C15-7-F,Mouser,621-BZT52C15-F
25,1,D14,GREEN,https://www.bivar.com/parts_content/Datasheets/SM1206NPGC-IL.pdf,LED_SM1206,Green 525nm LED Indication - Discrete 3V 1206 (3216 Metric),Bivar Inc.,SM1206NPGC-IL,Digikey,492-1945-1-ND
26,3,D19 D24 D25,Green,,LED_0603_1608Metric,Green 571nm LED Indication - Discrete 2V 0603 (1608 Metric),Lite-On,LTST-C191KGKT,Mouser,859-LTST-C191KGKT
27,2,D20 D21,PESD2CANFD24V-UX,https://assets.nexperia.com/documents/data-sheet/PESD2CANFD2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,SOT95P230X117-3N,42V Clamp 2.6A (8/20µs) Ipp Tvs Diode Surface Mount SOT-323,Nexperia USA Inc.,PESD2CANFD24V-UX,Digikey,1727-PESD2CANFD24V-UXCT-ND
28,1,D1,PESD4USB3U-TBSX,https://assets.nexperia.com/documents/data-sheet/PESD4USB3U-TBS.pdf,SOT1176D,"3.5V (Typ) Clamp 7A (8/20µs) Ipp Tvs Diode Surface Mount, Wettable Flank DFN2510D-10",Nexperia USA Inc.,PESD4USB3U-TBSX,Digikey,1727-PESD4USB3U-TBSXCT-ND
29,1,D22,PESD4USB5B,https://assets.nexperia.com/documents/data-sheet/PESD4USB5B-TBS.pdf,SOT1176D,"5.5V (Typ) Clamp 7A (8/20µs) Ipp Tvs Diode Surface Mount, Wettable Flank DFN2510D-10",Nexperia USA Inc.,PESD4USB5B-TBSX,Digikey,1727-PESD4USB5B-TBSXCT-ND
30,1,D17,PESD4USB5B-TBSX,https://assets.nexperia.com/documents/data-sheet/PESD4USB5B-TBS.pdf,SOT1176D,"5.5V (Typ) Clamp 7A (8/20µs) Ipp Tvs Diode Surface Mount, Wettable Flank DFN2510D-10",Nexperia USA Inc.,PESD4USB5B-TBSX,Digikey,1727-PESD4USB5B-TBSXCT-ND
31,1,D18,Red,,LED_0603_1608Metric,Red 631nm LED Indication - Discrete 2V 0603 (1608 Metric),Lite-On,LTST-C191KRKT,Mouser,859-LTST-C191KRKT
32,1,D2,SMBJ60A,https://www.littelfuse.com/assetdocs/tvs-diodes-smbj-series-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,D_SMB,"600 W unidirectional TVS, V_RWM 60 V, V_BR 66.7-73.7 V, V_C 96.8 V @ 6.2 A (10/1000 us), SMB (DO-214AA)",Littelfuse,SMBJ60A,Mouser,576-SMBJ60A
33,1,D13,YELLOW,https://www.bivar.com/parts_content/Datasheets/SM1206NYC-IL.pdf,LED_SM1206,Yellow 592nm LED Indication - Discrete 2V 1206 (3216 Metric),Bivar Inc.,SM1206NYC-IL,Digikey,492-1947-1-ND
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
